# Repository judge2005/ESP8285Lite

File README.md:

# ESP8285Lite
A bare-bones ESP8285 board that breaks out all of the GPIOs, including 9 and 10.

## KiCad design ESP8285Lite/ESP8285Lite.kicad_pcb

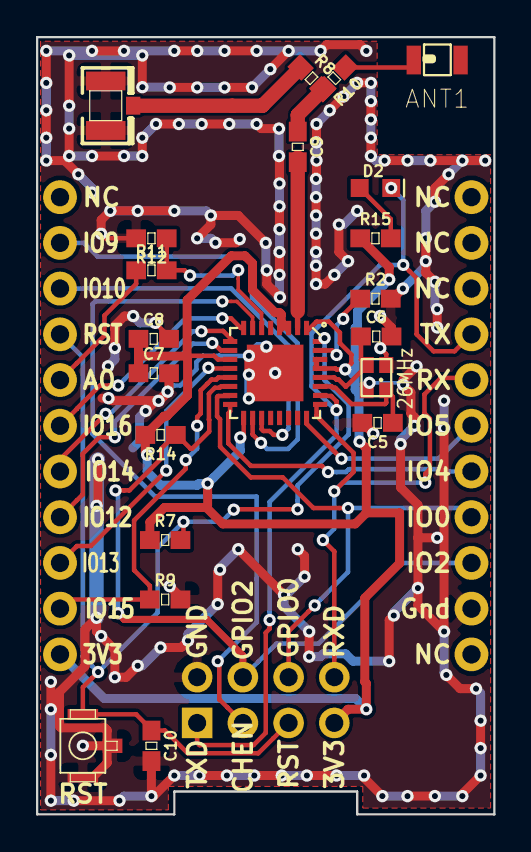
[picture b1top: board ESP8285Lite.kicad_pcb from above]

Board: 2 copper layers, 25.4 x 43.2 mm, 24 parts (1 on the bottom side), 27 nets.

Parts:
ANT1: 2450AT18B100E; ANT_2450AT18B100E
C5, C6: 12pF; SparkFun-Capacitors-0603
C7: 10uF; SparkFun-Capacitors-0603
C8: 100nF; SparkFun-Capacitors-0603
C9: 5.6pF; SparkFun-Capacitors-0603
C10: 0.1uF; SparkFun-Capacitors-0603
D2: LED-TX; SparkFun-LED-LED-0603
J1: LEFT; SparkFun-Connectors-1X11_NO_SILK_KIT
J2: RIGHT; SparkFun-Connectors-1X11_NO_SILK_KIT
J3: ESP01 Header; Socket_Strip_Straight_2x04_Pitch2.54mm
K1: RST; nixiemisc-B3U-1100P(M)
R2: 12K; SparkFun-Resistors-0603
R7, R9, R14: 10k; SparkFun-Resistors-0603
R8: DNP; SparkFun-Resistors-0603
R10: 0; SparkFun-Resistors-0603
R11: 220K; SparkFun-Resistors-0603
R12: 100K; SparkFun-Resistors-0603
R15: 470; SparkFun-Resistors-0603
U5: ESP8285QFN-32; nixiemisc-QFN-32
X1: ANTENNA_U.FL; adafruit-U.FL
Y1: 26MHz; nixiemisc-CRYSTAL2.0X1.6

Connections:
+3V3: C7.1, C8.1, J1.11, J3.7, R7.1, R14.2, R15.1, U5.1, U5.3, U5.4, U5.11, U5.17, U5.29, U5.30
A0: J1.5, R11.1
ADC: R11.2, R12.1, U5.6
CH_PD: J3.3, U5.7
GND: C5.2, C6.2, C7.2, C8.2, C10.2, J2.2, J3.2, K1.1, K1.GND, R2.2, R9.2, R12.2, U5.EP, X1.1, X1.2, Y1.2, Y1.4
GPIO0: J2.4, J3.6, U5.15
GPIO2: J2.3, J3.4, R14.1, U5.14
GPIO4: J2.5, U5.16
GPIO5: J2.6, U5.24
GPIO9: J1.2, U5.18
GPIO10: J1.3, U5.19
GPIO12: J1.8, U5.10
GPIO13: J1.9, U5.12
GPIO14: J1.7, U5.9
GPIO15: J1.10, R9.1, U5.13
GPIO16: J1.6, U5.8
unnamed: ANT1.1, R10.1
unnamed: C5.1, U5.27, Y1.1
unnamed: C6.1, U5.28, Y1.3
unnamed: C9.1, R8.2, R10.2
unnamed: C9.2, U5.2
unnamed: D2.A, R15.2
unnamed: R2.1, U5.31
unnamed: R8.1, X1.3
RST: C10.1, J1.4, J3.5, K1.2, R7.2, U5.32
RXD: J2.7, J3.8, U5.25
TXD: D2.C, J2.8, J3.1, U5.26
